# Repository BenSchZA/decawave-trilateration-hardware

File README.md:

# decawave-trilateration-hardware
Hardware (Kicad schematics and PCB) for a local vehicle tracking solution using trilateration and Decawave technology.

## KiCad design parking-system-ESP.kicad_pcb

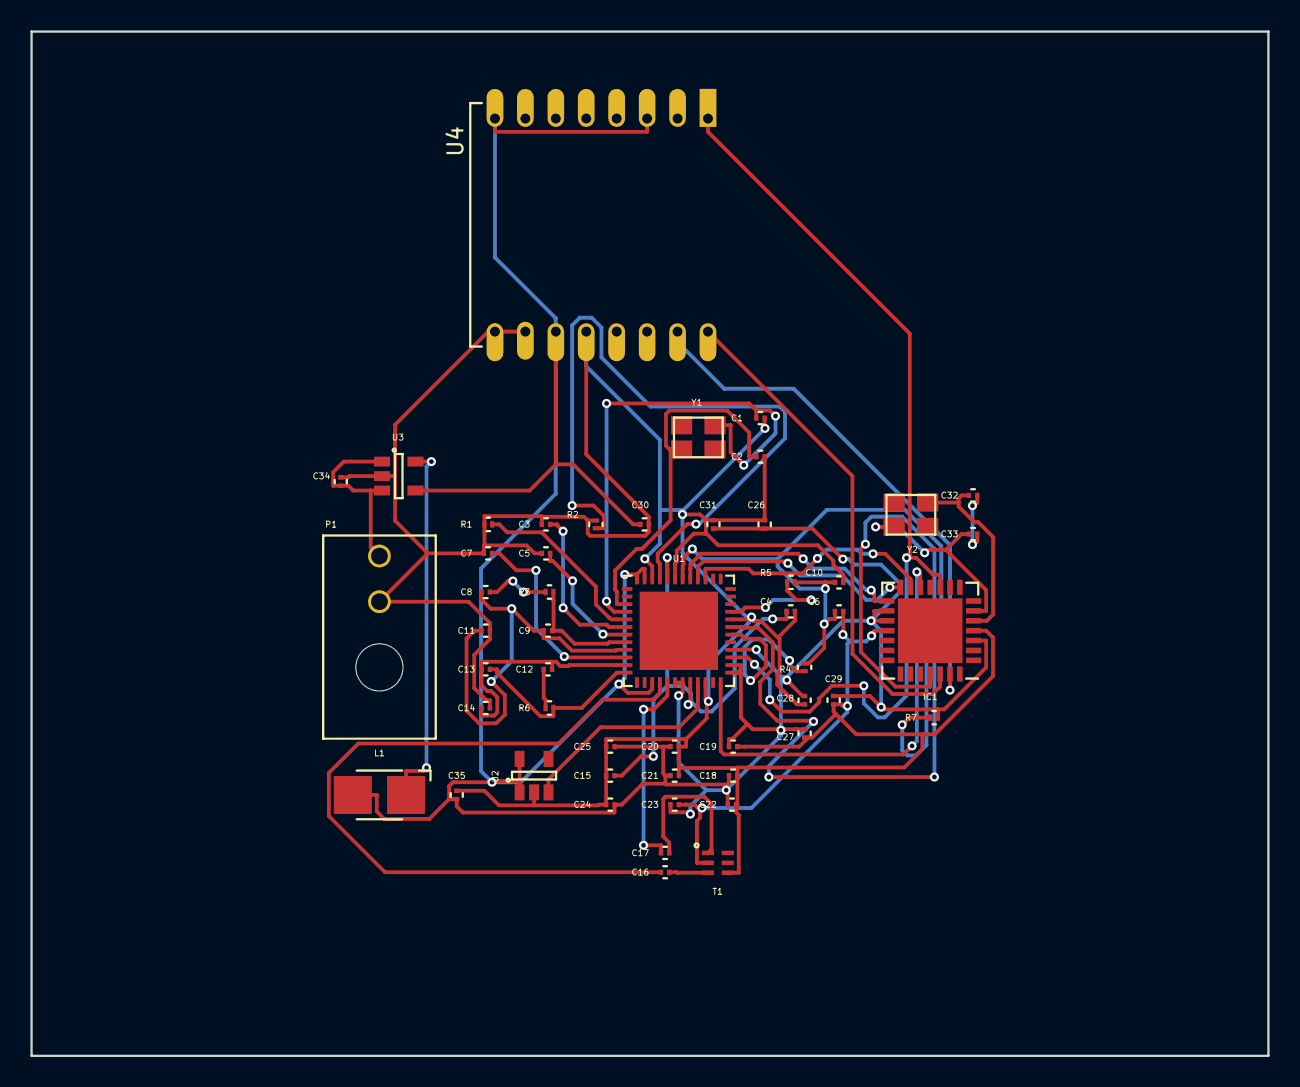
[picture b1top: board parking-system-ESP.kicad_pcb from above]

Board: 2 copper layers, 81.3 x 67.3 mm, 52 parts (0 on the bottom side), 37 nets.

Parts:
C1, C2, C20, C23: 10pF; C_0201
C3, C4, C5, C6, C7, C10, C11, C14, C15, C16, C17, C19, C22, C26, C27, C28, C29, C31: 0.1uF; C_0201
C8: 27pF; C_0201
C9: 1.2pF; C_0201
C12: 820pF; C_0201
C13: 18pF; C_0201
C18: 47uF; C_0201
C21, C24: 330pF; C_0201
C25: 1000pF; C_0201
C30, C34: 4.7uF; C_0201
C32, C33: 22pF; C_0201
C35: 10uF; C_0201
IC1: ATMEGA328P-MM; QFN-28-1EP_6x6mm_Pitch0.65mm
L1: 10uH; Inductor_1212
P1: CONN_01X02; Connector_Microfit3_Header_02x01_Angled_43045-020x
R1: 11k 1%; R_0201
R2: 100K; R_0201
R3: 16k; R_0201
R4, R5, R7: 10k; R_0201
R6: 270; R_0201
T1: TRANSFO4; HHM1595A1
U1: DW1000; QFN-48-1EP_7x7mm_Pitch0.5mm
U2, U3: TPS62203DBV; SOT-23-5
U4: ESP-12
Y1: 38.4MHz; crystal_FA238-TSX3225
Y2: 16MHz; crystal_FA238-TSX3225

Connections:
/DW1000-basic/BAT_LEVEL: C34.1, P1.2, U3.1, U3.3
/DW1000-basic/RESET: IC1.10, U1.27, U4.1
/ESP8266/RXD: IC1.27, U4.15
/micro/RXD: IC1.26, U4.16
CLKTUNE: C9.1, R3.1, U1.8
EXTON: U1.21, U2.3
GPIO5: R5.2, U1.33
GPIO6: R4.2, U1.30
IRQ: R2.1, U1.45
unnamed: C1.1, U1.4, Y1.2
unnamed: C2.1, U1.3, Y1.1
unnamed: C3.2, U1.6
unnamed: C5.2, U1.7
unnamed: C7.2, U1.10
unnamed: C8.1, R3.2
unnamed: C12.2, R6.1
unnamed: C16.1, T1.3
unnamed: C17.1, T1.1
unnamed: C32.2, C33.2
unnamed: IC1.25, R7.2
unnamed: L1.1, U3.5
unnamed: R1.2, U1.5
RF_N: C17.2, U1.17
RF_P: C16.2, U1.16
SPICLK: IC1.15, U1.41
SPICSn: IC1.12, U1.24
SPIMISO: IC1.14, U1.40
SPIMOSI: IC1.13, U1.39
VCOTUNE: C13.2, R6.2, U1.12
VDDAON: C18.1, C19.1, C20.1, C21.1, C22.1, C23.1, C24.1, C25.1, C26.1, C27.1, C28.1, C29.1, C30.1, C31.1, C35.1, IC1.3, IC1.16, IC1.17, L1.2, R7.1, U1.15, U1.18, U1.19, U1.25, U1.26, U1.28, U1.47, U1.48, U2.1, U2.5, U3.4, U4.3, U4.8, U4.11
VDDCLK: C8.2, C9.2, C11.1, U1.9
VDDDIG: C4.1, C15.1, U1.20, U1.44
VDDIO: C6.2, C10.1, R4.1, R5.1, U1.31, U1.42
VDDVCO: C12.1, C13.1, C14.1, U1.11
VSSIO: C1.2, C2.2, C3.1, C4.2, C5.1, C6.1, C7.1, C10.2, C11.2, C14.2, C15.2, C18.2, C19.2, C20.2, C21.2, C22.2, C23.2, C24.2, C25.2, C26.2, C27.2, C28.2, C29.2, C30.2, C31.2, C34.2, C35.2, IC1.4, IC1.18, P1.1, R1.1, R2.2, T1.2, T1.4, U1.22, U1.32, U1.43, U1.46, U2.2, U3.2, U4.9, U4.10, U4.12
XTAL1: C32.1, IC1.5, Y2.1
XTAL2: C33.1, IC1.6, Y2.2

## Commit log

2016-05-27 Remove ignored filed
2016-05-27 Removed gitignore files
